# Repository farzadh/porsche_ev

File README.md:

# porsche_ev
Repository for all firmware/software developments related to PORSCHE EV conversion

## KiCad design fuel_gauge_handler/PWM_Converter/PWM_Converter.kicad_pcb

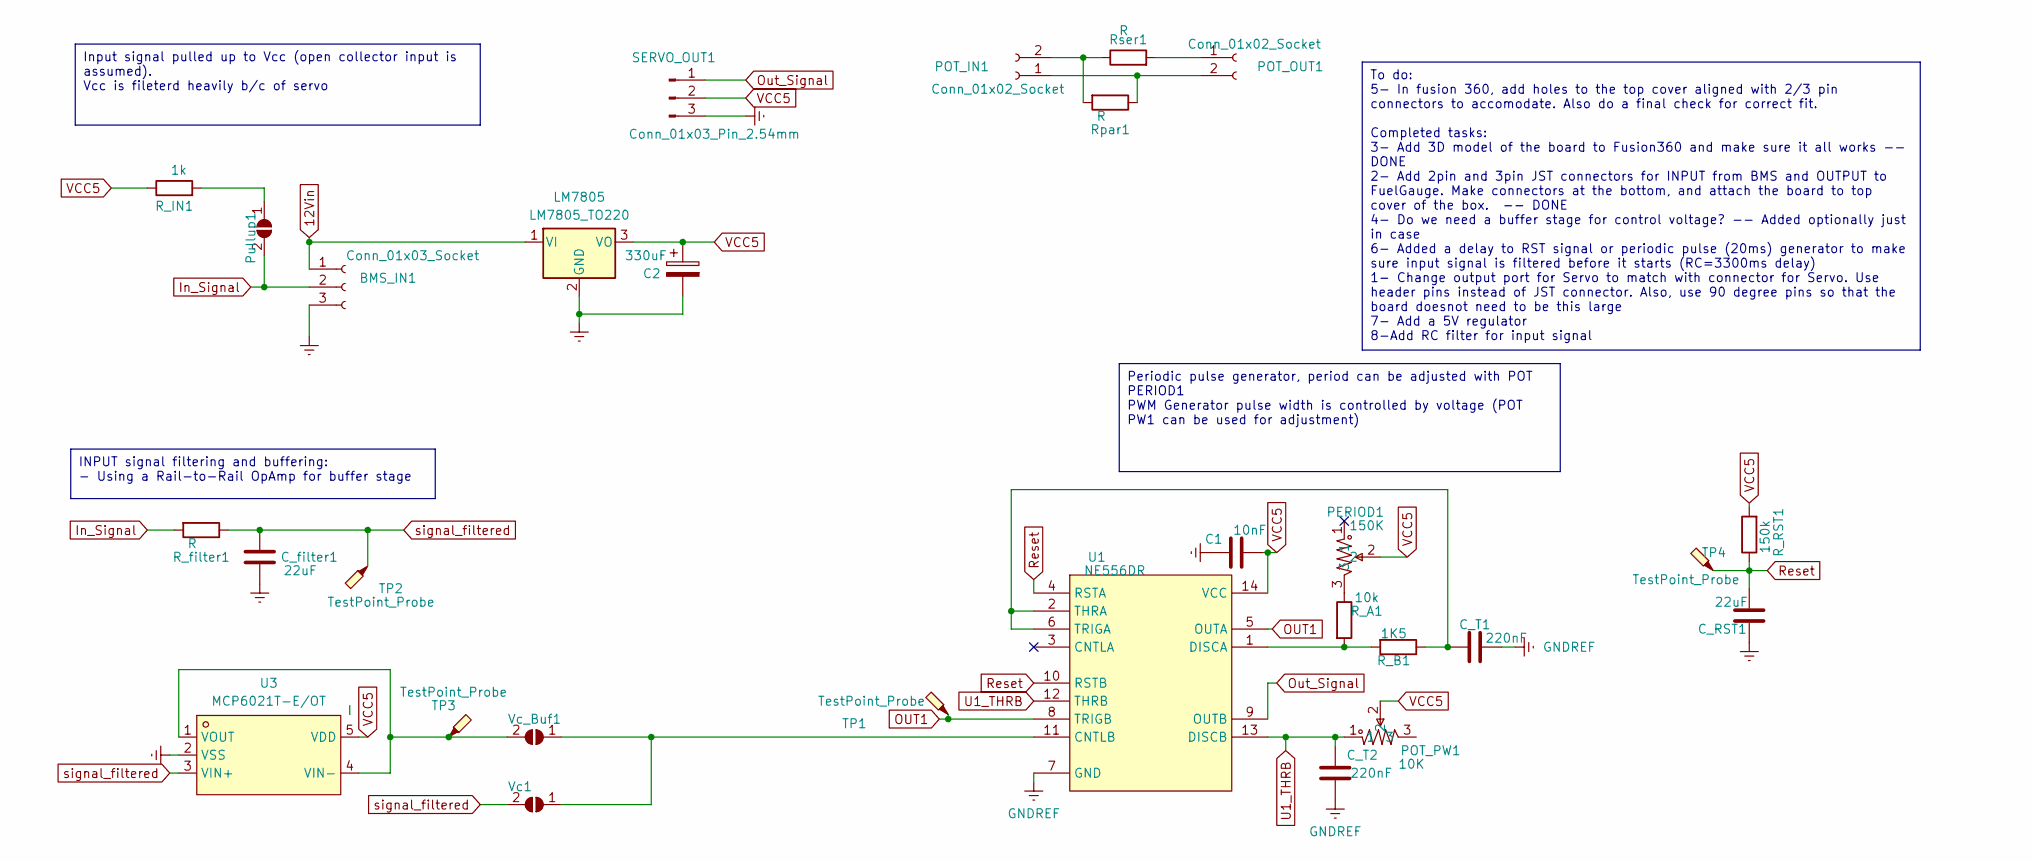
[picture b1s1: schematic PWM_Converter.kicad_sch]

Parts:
BMS_IN1: Conn_01x03_Socket; JST_PH_B3B-PH-K_1x03_P2.00mm_Vertical
C1: 10nF; C_0805_2012Metric; LCSC Param C1710
C2: 330uF; CP_Radial_D10.0mm_P5.00mm
C_RST1: 22uF; C_1206_3216Metric; LCSC Param C12891
C_T1, C_T2: 220nF; C_0805_2012Metric; LCSC Param C5378
C_filter1: 22uF; C_1206_3216Metric; LCSC Param C12891
LM7805: LM7805_TO220; TO-220-3_Vertical
PERIOD1: 150K; RES-ARRAY-TH_601030
POT_IN1: Conn_01x02_Socket; JST_PH_B2B-PH-K_1x02_P2.00mm_Vertical
POT_OUT1: Conn_01x02_Socket; JST_PH_B2B-PH-K_1x02_P2.00mm_Vertical
POT_PW1: 10K; RES-ARRAY-TH_601030
Pullup1: SolderJumper_2_Open; SolderJumper2_Open
R_A1: 10k; R_0805_2012Metric; LCSC Part C17414
R_B1: 1K5; R_0805_2012Metric; LCSC Part C4310
R_IN1: 1k; R_0805_2012Metric; LCSC Part C17513
R_RST1: 150k; R_0805_2012Metric; LCSC Part C17470
R_filter1: R; R_Axial_DIN0207_L6.3mm_D2.5mm_P10.16mm_Horizontal
Rpar1: R; R_Axial_DIN0207_L6.3mm_D2.5mm_P10.16mm_Horizontal
Rser1: R; R_Axial_DIN0207_L6.3mm_D2.5mm_P10.16mm_Horizontal
SERVO_OUT1: Conn_01x03_Pin_2.54mm; PinHeader_1x03_P2.54mm_Horizontal
TP1, TP2, TP3, TP4: TestPoint_Probe; TestPoint_Pad_1.5x1.5mm
U1: NE556DR; SOIC-14_L8.7-W3.9-P1.27-LS6.0-BL; LCSC Part C7427
U3: MCP6021T-E/OT; SOT-23-5_L3.0-W1.7-P0.95-LS2.8-BR; LCSC Part C50538
Vc1: SolderJumper_2_Open; SolderJumper2_Open
Vc_Buf1: SolderJumper_2_Open; SolderJumper2_Open

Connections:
12Vin: BMS_IN1.1, LM7805.1 (VI)
GNDREF: BMS_IN1.3, C1.1, C2.2, C_RST1.1, C_T1.1, C_T2.1, C_filter1.1, LM7805.2 (GND), SERVO_OUT1.3, U1.7 (GND), U3.2 (VSS)
In_Signal: BMS_IN1.2, Pullup1.2 (B), R_filter1.2
unnamed: PERIOD1.3, R_A1.1
unnamed: POT_IN1.1, POT_OUT1.2, Rpar1.1
unnamed: POT_IN1.2, Rpar1.2, Rser1.1
unnamed: POT_OUT1.1, Rser1.2
unnamed: Pullup1.1 (A), R_IN1.2
unnamed: U1.11 (CNTLB), Vc1.1 (A), Vc_Buf1.1 (A)
unnamed: R_A1.2, R_B1.2, U1.1 (DISCA)
unnamed: C_T1.2, R_B1.1, U1.2 (THRA), U1.6 (TRIGA)
unnamed: TP3.1, U3.1 (VOUT), U3.4 (VIN-), Vc_Buf1.2 (B)
OUT1: TP1.1, U1.5 (OUTA), U1.8 (TRIGB)
Out_Signal: SERVO_OUT1.1, U1.9 (OUTB)
Reset: C_RST1.2, R_RST1.1, TP4.1, U1.4 (RSTA), U1.10 (RSTB)
U1_THRB: C_T2.2, POT_PW1.1, U1.12 (THRB), U1.13 (DISCB)
VCC5: C1.2, C2.1, LM7805.3 (VO), PERIOD1.2, POT_PW1.2, R_IN1.1, R_RST1.2, SERVO_OUT1.2, U1.14 (VCC), U3.5 (VDD)
signal_filtered: C_filter1.2, R_filter1.1, TP2.1, U3.3 (VIN+), Vc1.2 (B)

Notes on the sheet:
To do: 5- In fusion 360, add holes to the top cover aligned with 2/3 pin connectors to accomodate. Also do a final check for correct fit. Completed tasks: 3- Add 3D model of the board to Fusion360 and make sure it all works -- DONE 2- Add 2pin and 3pin JST connectors for INPUT from BMS and OUTPUT t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
Periodic pulse generator, period can be adjusted with POT PERIOD1 PWM Generator pulse width is controlled by voltage (POT PW1 can be used for adjustment)
Input signal pulled up to Vcc (open collector input is assumed). Vcc is fileterd heavily b/c of servo
INPUT signal filtering and buffering: - Using a Rail-to-Rail OpAmp for buffer stage

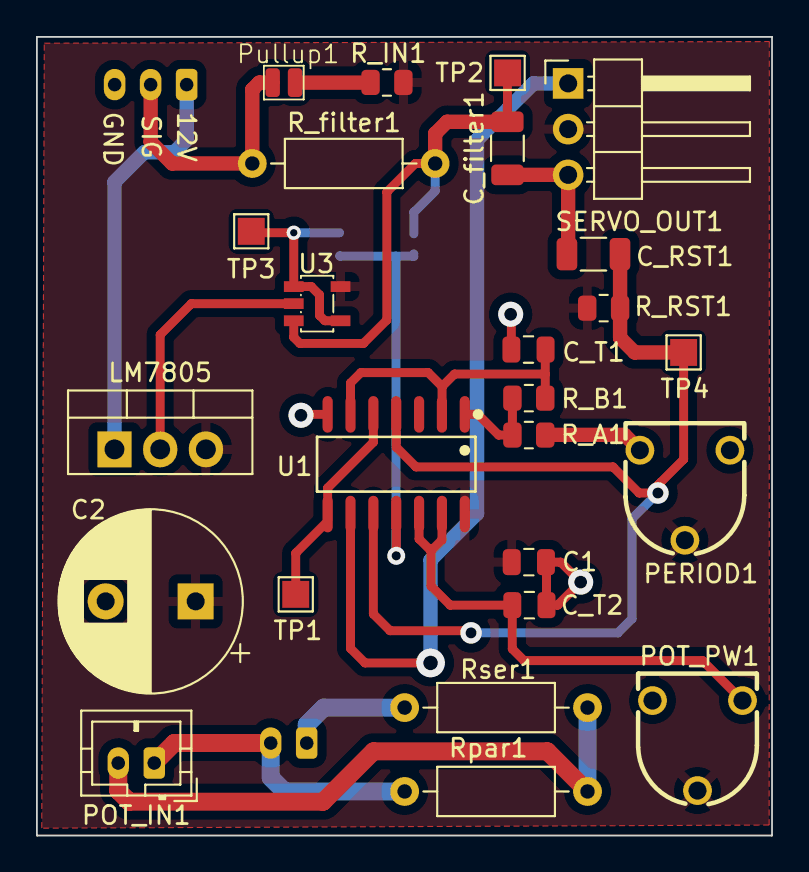
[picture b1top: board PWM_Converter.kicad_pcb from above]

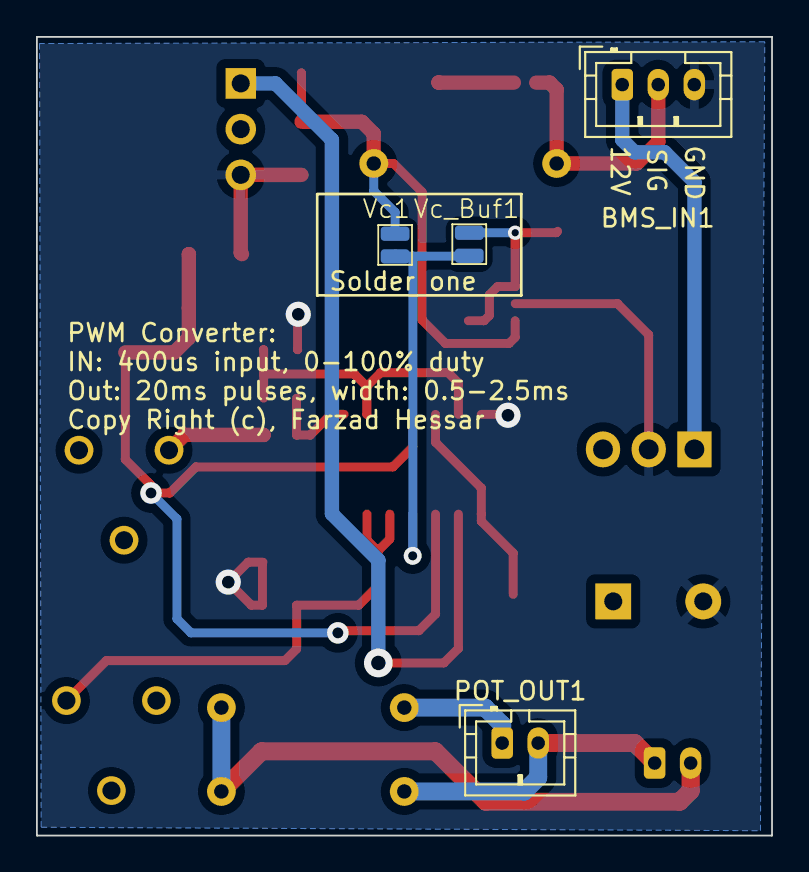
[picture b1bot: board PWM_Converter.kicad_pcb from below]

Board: 2 copper layers, 40.8 x 44.4 mm, 29 parts (4 on the bottom side), 18 nets.

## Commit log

2024-11-22 Add VCU code for Arduino Due
2024-11-22 Update project folder
2024-11-22 Added error recovery, sensor reading, and temperature reporting
2024-11-22 Fix error status during recovery
2024-11-22 Reset interrupt timers
2024-12-20 Adding CAN DBC files for DCDC message
2024-12-20 Fix DCDC CAN DBC file
2024-12-26 Added OBC message definitions for ELCON
2025-01-02 Add support for charger, CAN messages, and DBC updates
2025-01-03 Add CAN support for DCDC + display updates
2025-07-23 First version of PWM converter
2025-07-24 Add symbol analyzer checking
2025-07-24 Add checkers for 3D symbol library
